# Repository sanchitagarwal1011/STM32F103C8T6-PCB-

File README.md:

# KiCad STM32 PCB Design — Phil’s Lab #65

A PCB design project created while following **Phil’s Lab #65: STM32 PCB Design Tutorial**.

This project was developed as a practical exercise to learn the complete PCB design workflow using KiCad.

## Project Overview

The project covers the design of an STM32-based PCB, including schematic creation, component selection, footprint assignment, PCB layout, routing, and design-rule checking.

## What I Practiced

* Schematic design in KiCad
* STM32 microcontroller integration
* Component and footprint selection
* PCB component placement
* Power and ground routing
* Signal routing
* Track-width selection
* Ground-plane creation
* PCB design-rule checking
* Gerber file generation
* Basic PCB documentation

## Software Used

* KiCad 10
* Git
* GitHub

## Project Files

The repository contains the following KiCad files:

* KiCad project file
* Schematic file
* PCB layout file
* Gerber manufacturing files
* Project documentation

## PCB Design Preview

### Schematic

### PCB Layout

### 3D View

## Project Status

* [x] Schematic completed
* [x] Components selected
* [x] Footprints assigned
* [x] PCB layout created
* [x] Components placed
* [x] PCB routing completed
* [x] Ground plane added
* [x] Design-rule checking completed
* [x] Gerber files generated
* [ ] PCB manufacturing
* [ ] Hardware testing

## Learning Reference

This project is based on:

**Phil’s Lab — Lesson #65: STM32 PCB Design Tutorial**

The project is intended for educational and personal PCB-design practice.

## Disclaimer

This PCB has been created as a learning project. It has not been manufactured or hardware-tested, and it should not be used in a real application without further verification and testing.

## Author

**Sanchit Agarwal**

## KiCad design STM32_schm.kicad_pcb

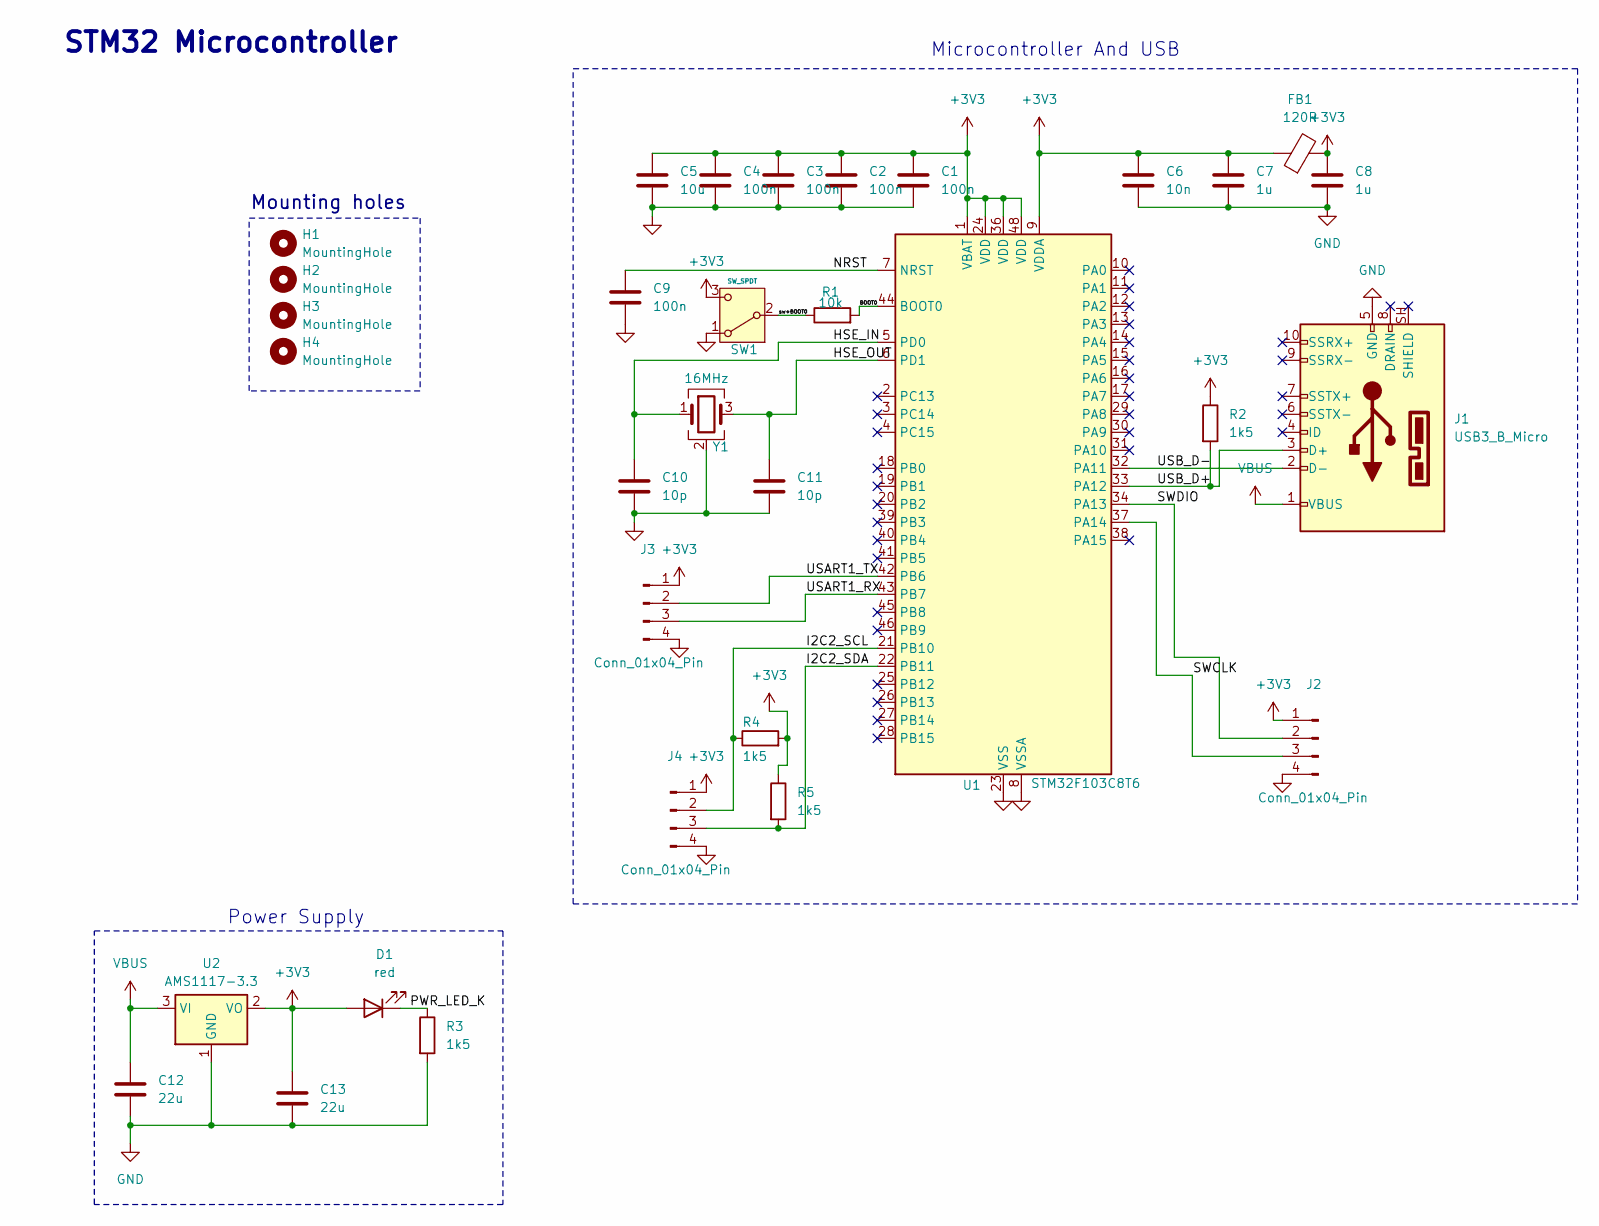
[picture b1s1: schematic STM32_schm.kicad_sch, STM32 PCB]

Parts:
C1, C2, C3, C4, C9: 100n; C_0402_1005Metric
C5: 10u; C_0603_1608Metric
C6: 10n; C_0402_1005Metric
C7, C8: 1u; C_0402_1005Metric
C10, C11: 10p; C_0402_1005Metric
C12, C13: 22u; C_0805_2012Metric
D1: red; LED_0603_1608Metric
FB1: 120R; L_0603_1608Metric
H1, H2, H3, H4: MountingHole; MountingHole_2.1mm
J1: USB3_B_Micro; USB_Micro-B_Wuerth_629105150521
J2, J3, J4: Conn_01x04_Pin; PinHeader_1x04_P2.54mm_Vertical
R1: 10k; R_0402_1005Metric
R2, R3, R4, R5: 1k5; R_0402_1005Metric
SW1: SW_SPDT; SW_SPDT_PCM12
U1: STM32F103C8T6; LQFP-48_7x7mm_P0.5mm
U2: AMS1117-3.3; SOT-223-3_TabPin2
Y1: 16MHz; Crystal_SMD_3225-4Pin_3.2x2.5mm

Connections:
+3V3: C1.1, C2.1, C3.1, C4.1, C5.1, C6.1, C7.1, C8.1, C13.1, D1.2 (A), FB1.1, FB1.2, J2.1, J3.1, J4.1, R2.1, R4.2, R5.1, SW1.3 (C), U1.1 (VBAT), U1.9 (VDDA), U1.24 (VDD), U1.36 (VDD), U1.48 (VDD), U2.2 (VO)
/BOOT0: R1.2, U1.44 (BOOT0)
/HSE_IN: C10.1, U1.5 (PD0), Y1.1
/HSE_OUT: C11.1, U1.6 (PD1), Y1.3
/I2C2_SCL: J4.2, R4.1, U1.21 (PB10)
/I2C2_SDA: J4.3, R5.2, U1.22 (PB11)
/NRST: C9.1, U1.7 (NRST)
/PWR_LED_K: D1.1 (K), R3.1
/SWCLK: J2.3, U1.37 (PA14)
/SWDIO: J2.2, U1.34 (PA13)
/USART1_RX: J3.3, U1.43 (PB7)
/USART1_TX: J3.2, U1.42 (PB6)
/USB_D+: J1.3 (D+), R2.2, U1.33 (PA12)
/USB_D-: J1.2 (D-), U1.32 (PA11)
/sw+BOOT0: R1.1, SW1.2 (B)
GND: C1.2, C2.2, C3.2, C4.2, C5.2, C6.2, C7.2, C8.2, C9.2, C10.2, C11.2, C12.2, C13.2, J1.5 (GND), J2.4, J3.4, J4.4, R3.2, SW1.1 (A), U1.8 (VSSA), U1.23 (VSS), U1.35 (VSS), U1.47 (VSS), U2.1 (GND), Y1.2 (G), Y1.4 (G)
VBUS: C12.1, J1.1 (VBUS), U2.3 (VI)

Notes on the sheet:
STM32 Microcontroller
Power Supply
Mounting holes
Microcontroller And USB

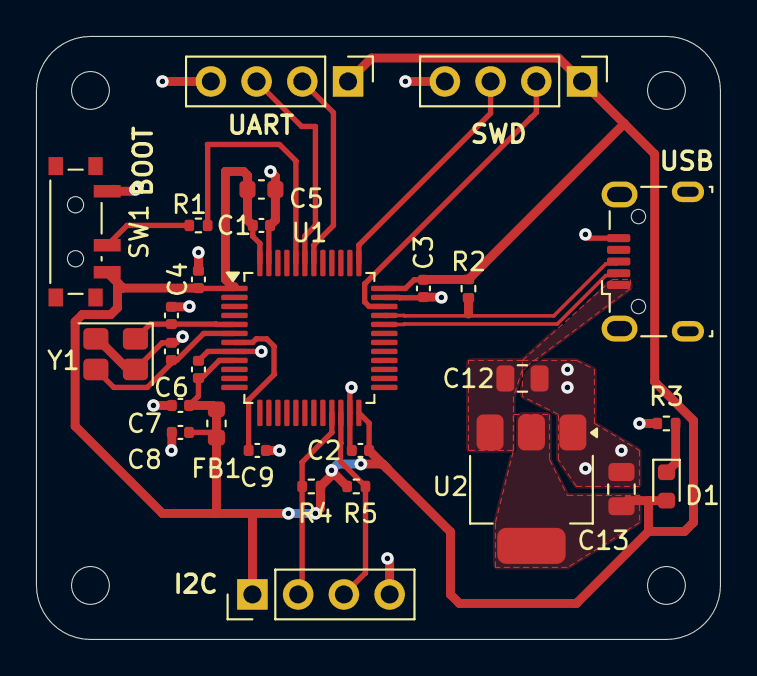
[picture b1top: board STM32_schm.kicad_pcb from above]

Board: 2 copper layers, 38.0 x 33.5 mm, 32 parts (0 on the bottom side), 17 nets.
